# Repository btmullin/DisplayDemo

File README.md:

# Display Demo

This project contains the basics for a quick POC on a 3d printed dual material
display.  Uses PC for the windows and ASA for the body.  Includes basic design
files for a POC board with WS2812 LEDs.

## Links

- [Repo](...)
- [Live](...)
- [Bugs](...)

## Screenshots

## Usage

## Built With

## Author

**Ben Mullin**

- [Profile](https://github.com/btmullin)
- [Email](mailto:benjamin.t.mullin@gmail.com)

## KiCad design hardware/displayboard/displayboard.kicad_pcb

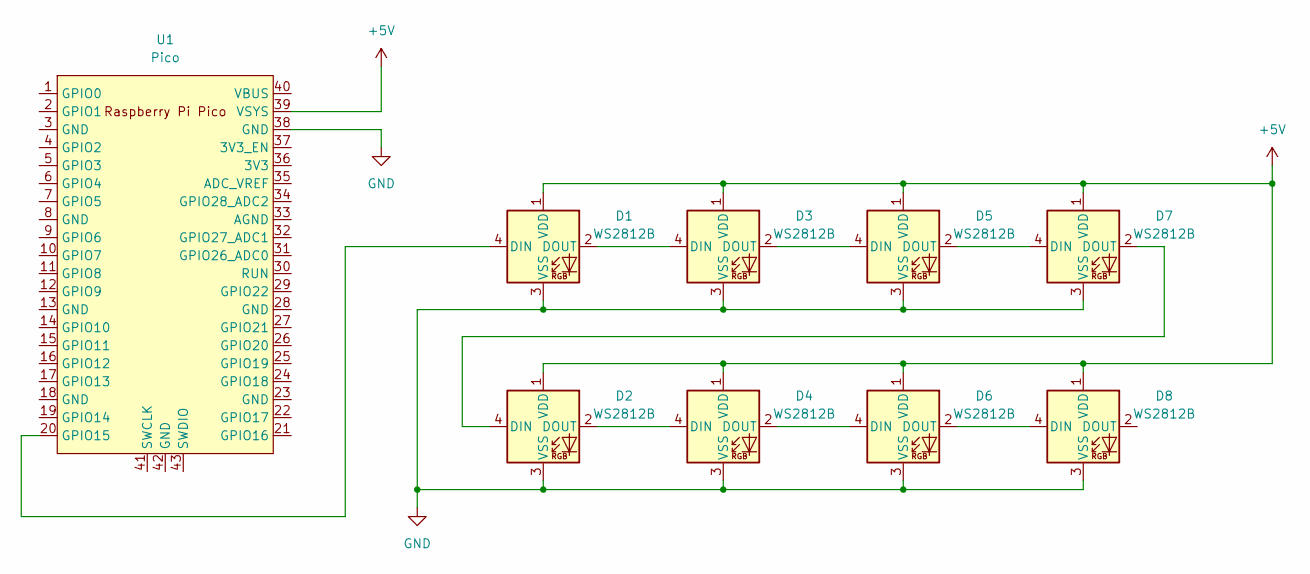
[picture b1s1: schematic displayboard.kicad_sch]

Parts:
D1, D2, D3, D4, D5, D6, D7, D8: WS2812B; LED_WS2812B_PLCC4_5.0x5.0mm_P3.2mm
U1: Pico; RPi_Pico_SMD_TH

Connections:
+5V: D1.1 (VDD), D2.1 (VDD), D3.1 (VDD), D4.1 (VDD), D5.1 (VDD), D6.1 (VDD), D7.1 (VDD), D8.1 (VDD), U1.39 (VSYS)
GND: D1.3 (VSS), D2.3 (VSS), D3.3 (VSS), D4.3 (VSS), D5.3 (VSS), D6.3 (VSS), D7.3 (VSS), D8.3 (VSS), U1.38 (GND)
unnamed: D1.2 (DOUT), D3.4 (DIN)
unnamed: D1.4 (DIN), U1.20 (GPIO15)
unnamed: D2.2 (DOUT), D4.4 (DIN)
unnamed: D2.4 (DIN), D7.2 (DOUT)
unnamed: D3.2 (DOUT), D5.4 (DIN)
unnamed: D4.2 (DOUT), D6.4 (DIN)
unnamed: D5.2 (DOUT), D7.4 (DIN)
unnamed: D6.2 (DOUT), D8.4 (DIN)

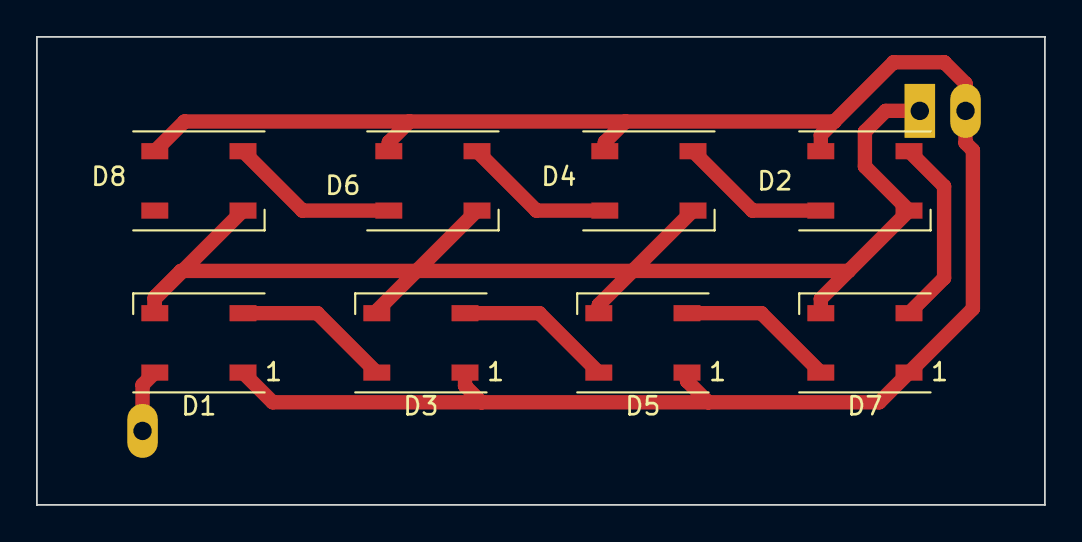
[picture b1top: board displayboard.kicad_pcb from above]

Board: 2 copper layers, 56.0 x 26.0 mm, 9 parts (1 on the bottom side), 10 nets.

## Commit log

2022-04-06 Initial directory structure and document templates
    This is the initial proposed directory structure and has the very
    first template design documents.
2022-04-07 Adding .gitignore
    Added a git ignore that has the patterns to ignore the KiCad
    backup and cache files
2023-06-26 Better ignores
2023-06-26 Added project description
2023-06-27 Cache ignore on KiCad
2023-06-27 Basic rectangular board with RPico and 8 leds
